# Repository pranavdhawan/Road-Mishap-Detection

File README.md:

# road-mishap

## Statistics

According to 2021 data, the country had 467,044 accidents, with 151,417 people killed and 469,418 people injured. It also means that 17 people have died and 53 have been injured every hour in India.

There is full-size statistical proof that points to driver drowsiness as a main cause of road accidents all over the world. Driving for prolonged intervals of time can lead to accidents if rest is no longer taken. Drowsiness is an important purpose of vehicular accidents.

## Abstract 

The Detection of Road Mishaps project aims to develop a comprehensive system for detecting and preventing road accidents. The project utilizes Internet of Things (IoT) technology to create three essential modules: Speed Calculator, Gas Detection, and Crash Detection. By combining these modules, the project aims to improve road safety by providing real-time data and alerts to both drivers and authorities, facilitating proactive measures to prevent mishaps.

## Tech Stack

- TinkerCAD and Wokwi Simulation
- Arduino and sensors
- HTML, CSS, JS
- Google Cloud API
- Eagle for PCB Design

### Speed Calculator Module:

*Purpose*: This module is responsible for monitoring and calculating the speed of vehicles on the road. It helps in identifying vehicles that are exceeding speed limits, which can lead to accidents.

*Electronics*: The Speed Calculator module includes components such as ultrasonic sensors or radar sensors to measure the speed of passing vehicles.

*Firmware Design*: The firmware for this module is designed to read data from the sensors, calculate vehicle speed, and transmit this information to a central processing unit. The firmware should also include logic for setting speed limits and generating alerts when violations occur.

### Gas Detection Module:

*Purpose*: This module detects and monitors harmful gases, such as carbon monoxide (CO) and nitrogen oxides (NOx), which can be emitted from vehicles and pose health risks to both drivers and pedestrians.

*Electronics*: Gas sensors like CO and NOx detectors are used to monitor air quality and detect the presence of dangerous gases.

*Firmware Design*: The firmware for this module reads data from the gas sensors, processes the data to determine gas concentration levels, and triggers alerts if hazardous levels are detected. It should also include calibration routines to ensure accurate measurements.

### Crash Detection Module:

*Purpose*: This module is responsible for detecting vehicle collisions or accidents on the road. It plays a crucial role in rapidly alerting authorities and emergency services.

*Electronics*: Accelerometers and impact sensors are typically used to detect sudden changes in vehicle velocity or impacts.

*Firmware Design*: The firmware for this module continuously monitors the accelerometer data. When a significant change in velocity or an impact is detected, it triggers an alarm or sends an emergency notification to authorities and nearby drivers. It should also incorporate GPS data to provide the accident's location

### [Speed Calculator](https://wokwi.com/projects/366746748629807105)

### [Gas Detection](https://www.tinkercad.com/things/bBwrbBcnv4k)

### [Crash Detection](https://www.tinkercad.com/things/hjC9y57r7hT)

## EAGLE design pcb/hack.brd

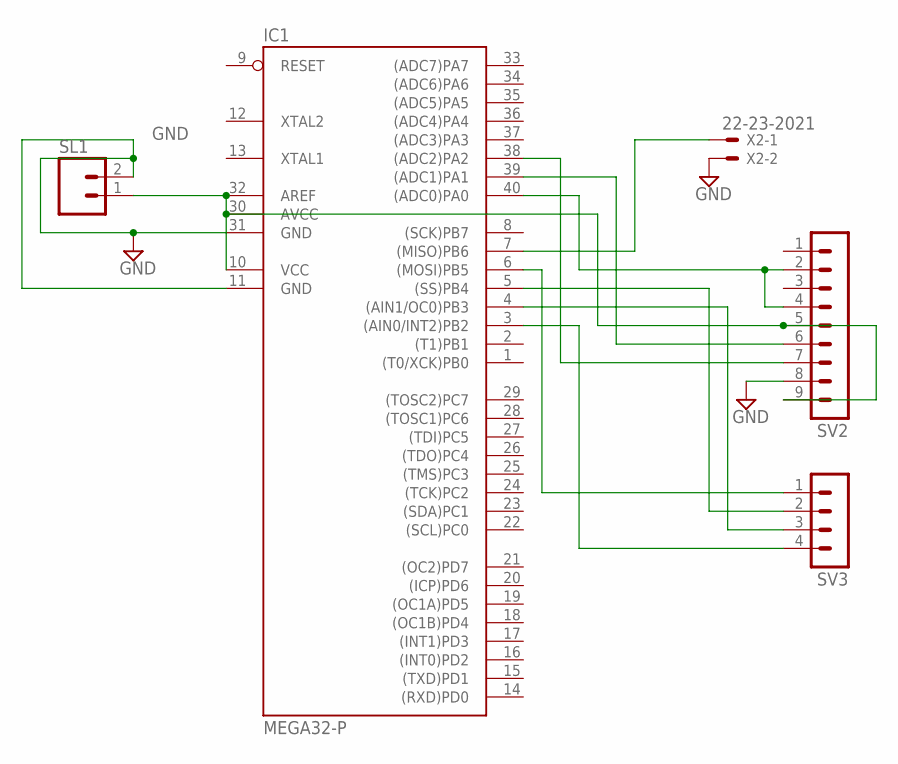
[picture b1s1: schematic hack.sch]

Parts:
IC1: MEGA32-P; DIL40
SL1: M02; 02P
SV2: MA09-1W
SV3: MA04-1
X2: 22-23-2021

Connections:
GND: IC1.11 (GND), IC1.31 (GND), SL1.2, SV2.8, X2.2
unnamed: IC1.7 ((MISO)PB6), X2.1
unnamed: IC1.6 ((MOSI)PB5), SV3.1
unnamed: IC1.5 ((SS)PB4), SV3.2
unnamed: IC1.40 ((ADC0)PA0), SV2.2, SV2.4
unnamed: IC1.10 (VCC), IC1.30 (AVCC), IC1.32 (AREF), SL1.1, SV2.5, SV2.9
unnamed: IC1.39 ((ADC1)PA1), SV2.6
unnamed: IC1.38 ((ADC2)PA2), SV2.7
unnamed: IC1.4 ((AIN1/OC0)PB3), SV3.3
unnamed: IC1.3 ((AIN0/INT2)PB2), SV3.4

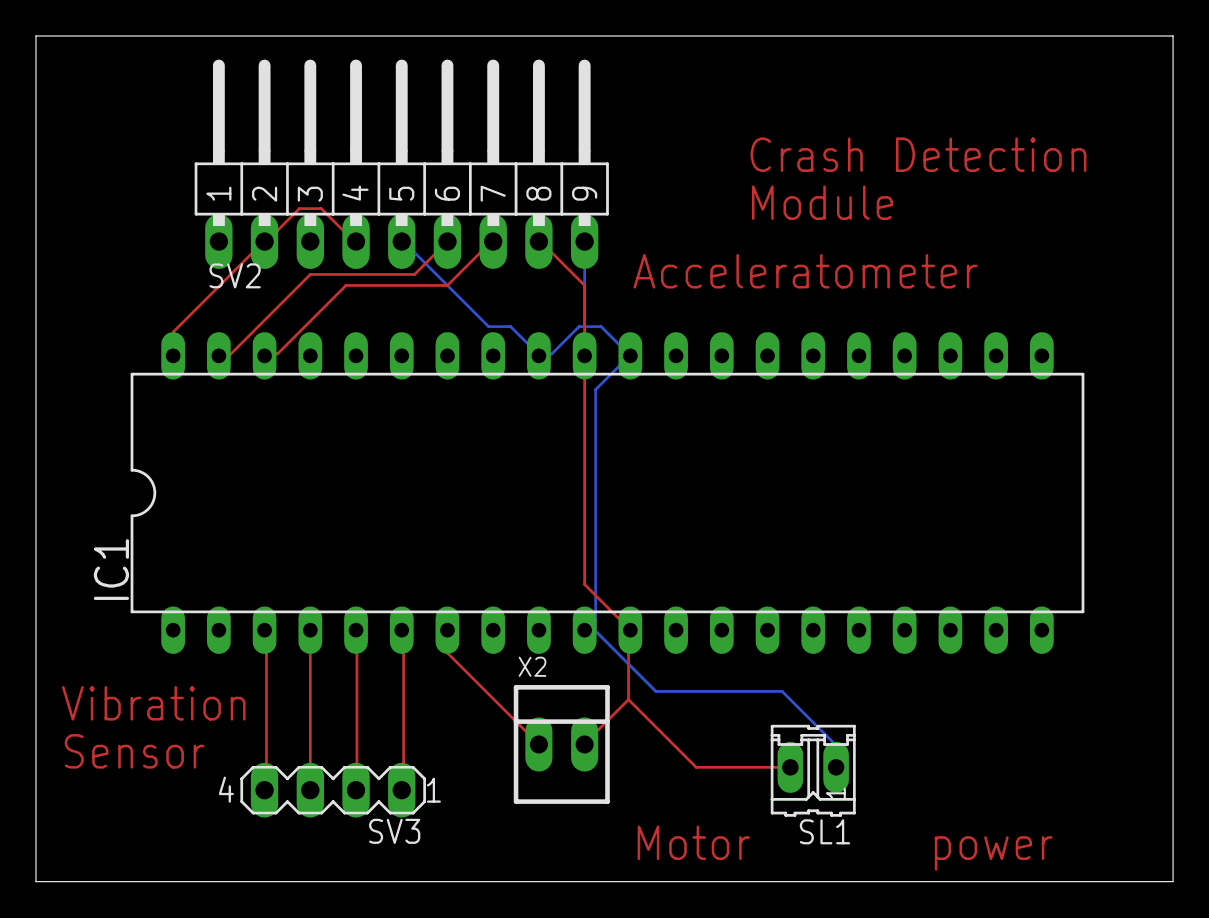
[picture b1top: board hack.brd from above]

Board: 2 copper layers, 63.2 x 47.0 mm, 5 parts (0 on the bottom side), 10 nets.

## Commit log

2023-06-06 init
2023-06-06 DSafs
2023-06-07 Added PCB files
